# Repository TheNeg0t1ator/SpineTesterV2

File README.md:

# SpineTesterV2
A spine tester purely based uppon python that can get the spine, 
center of gravity and weight of an arrow.
This is done by two HX711 amplifiers and strain gauges.

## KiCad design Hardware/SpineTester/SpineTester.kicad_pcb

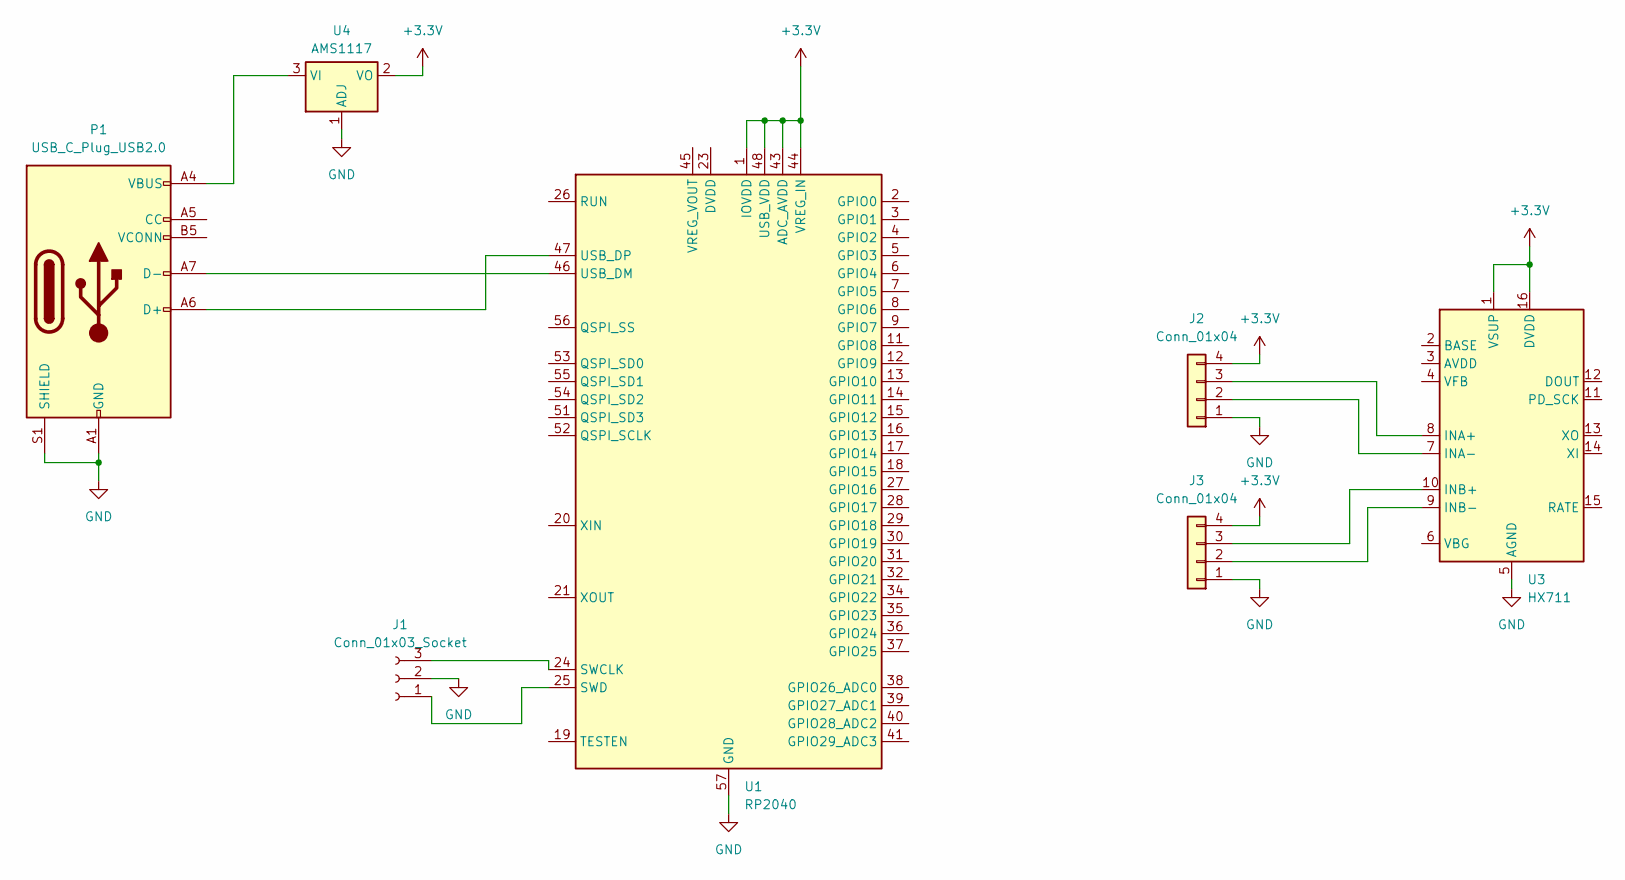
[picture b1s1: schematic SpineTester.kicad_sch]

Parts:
J1: Conn_01x03_Socket; JST_SH_BM03B-SRSS-TB_1x03-1MP_P1.00mm_Vertical
J2, J3: Conn_01x04; Solderpad
P1: USB_C_Plug_USB2.0; USB_C_Receptacle_JAE_DX07S016JA1R1500
U1: RP2040; QFN-56-1EP_7x7mm_P0.4mm_EP3.2x3.2mm
U3: HX711; SOP-16_3.9x9.9mm_P1.27mm
U4: AMS1117; SOT-223-3_TabPin2

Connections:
+3.3V: J2.4, J3.4, U1.1 (IOVDD), U1.10 (IOVDD), U1.22 (IOVDD), U1.33 (IOVDD), U1.42 (IOVDD), U1.43 (ADC_AVDD), U1.44 (VREG_IN), U1.48 (USB_VDD), U1.49 (IOVDD), U3.1 (VSUP), U3.16 (DVDD), U4.2 (VO)
GND: J1.2, J2.1, J3.1, P1.A1 (GND), P1.A12 (GND), P1.B1 (GND), P1.B12 (GND), P1.S1 (SHIELD), U1.57 (GND), U3.5 (AGND), U4.1 (ADJ)
unnamed: J1.1, U1.25 (SWD)
unnamed: J1.3, U1.24 (SWCLK)
unnamed: J2.2, U3.7 (INA-)
unnamed: J2.3, U3.8 (INA+)
unnamed: J3.2, U3.9 (INB-)
unnamed: J3.3, U3.10 (INB+)
unnamed: P1.A6 (D+), U1.47 (USB_DP)
unnamed: P1.A7 (D-), U1.46 (USB_DM)
unnamed: U1.23 (DVDD), U1.50 (DVDD)
unnamed: P1.A4 (VBUS), P1.A9 (VBUS), P1.B4 (VBUS), P1.B9 (VBUS), U4.3 (VI)

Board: 2 copper layers, 7 parts (0 on the bottom side), 12 nets, no tracks yet.

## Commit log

2024-09-20 changed the getweight to the uart class.
2024-09-20 :100:
2024-09-24 added device prototype
2024-10-22 edit readme
2025-06-17 create project
2025-06-17 initial pcb commit
2025-06-26 added connectors
2025-08-05 changed connectors
2025-08-05 update, works with one using pio
2025-08-05 working with two sensors
